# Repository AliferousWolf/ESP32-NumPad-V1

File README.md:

Included are all the files for the PCB and parts of the numpad v1 (Arduino IDE and KiCad)
------------------------
This is technically a prototype. The code is from various libraries and not very optomized, but it is a place to start.
To flash the ESP32 with the code, I used ArduinoIDE with the ESP32 boards added. When flashing, don't forget to download the libraries used within the code.

Parts used (part number):
------------------------
ESP 32 (NodeMCU-32S)
2x Encoder (PEC11L-4115F-S0020)
22x SMD diode (1N4148WS)
TFT display (Adafruit 4383)
mini sd card for tft display (technically optional)
24x mx switches depending on configuration
2x stabilizors depending on configuration

Optional for batery/bluetooth (part number)
------------------------
Switch (EG2208)
2x Capacitor 1uF (VJ1206Y105JXQTW1BC)
3.3v regulator (TC1264-3.3VDB)
10k resistor
6.8k resistor
3.3k resistor
battery

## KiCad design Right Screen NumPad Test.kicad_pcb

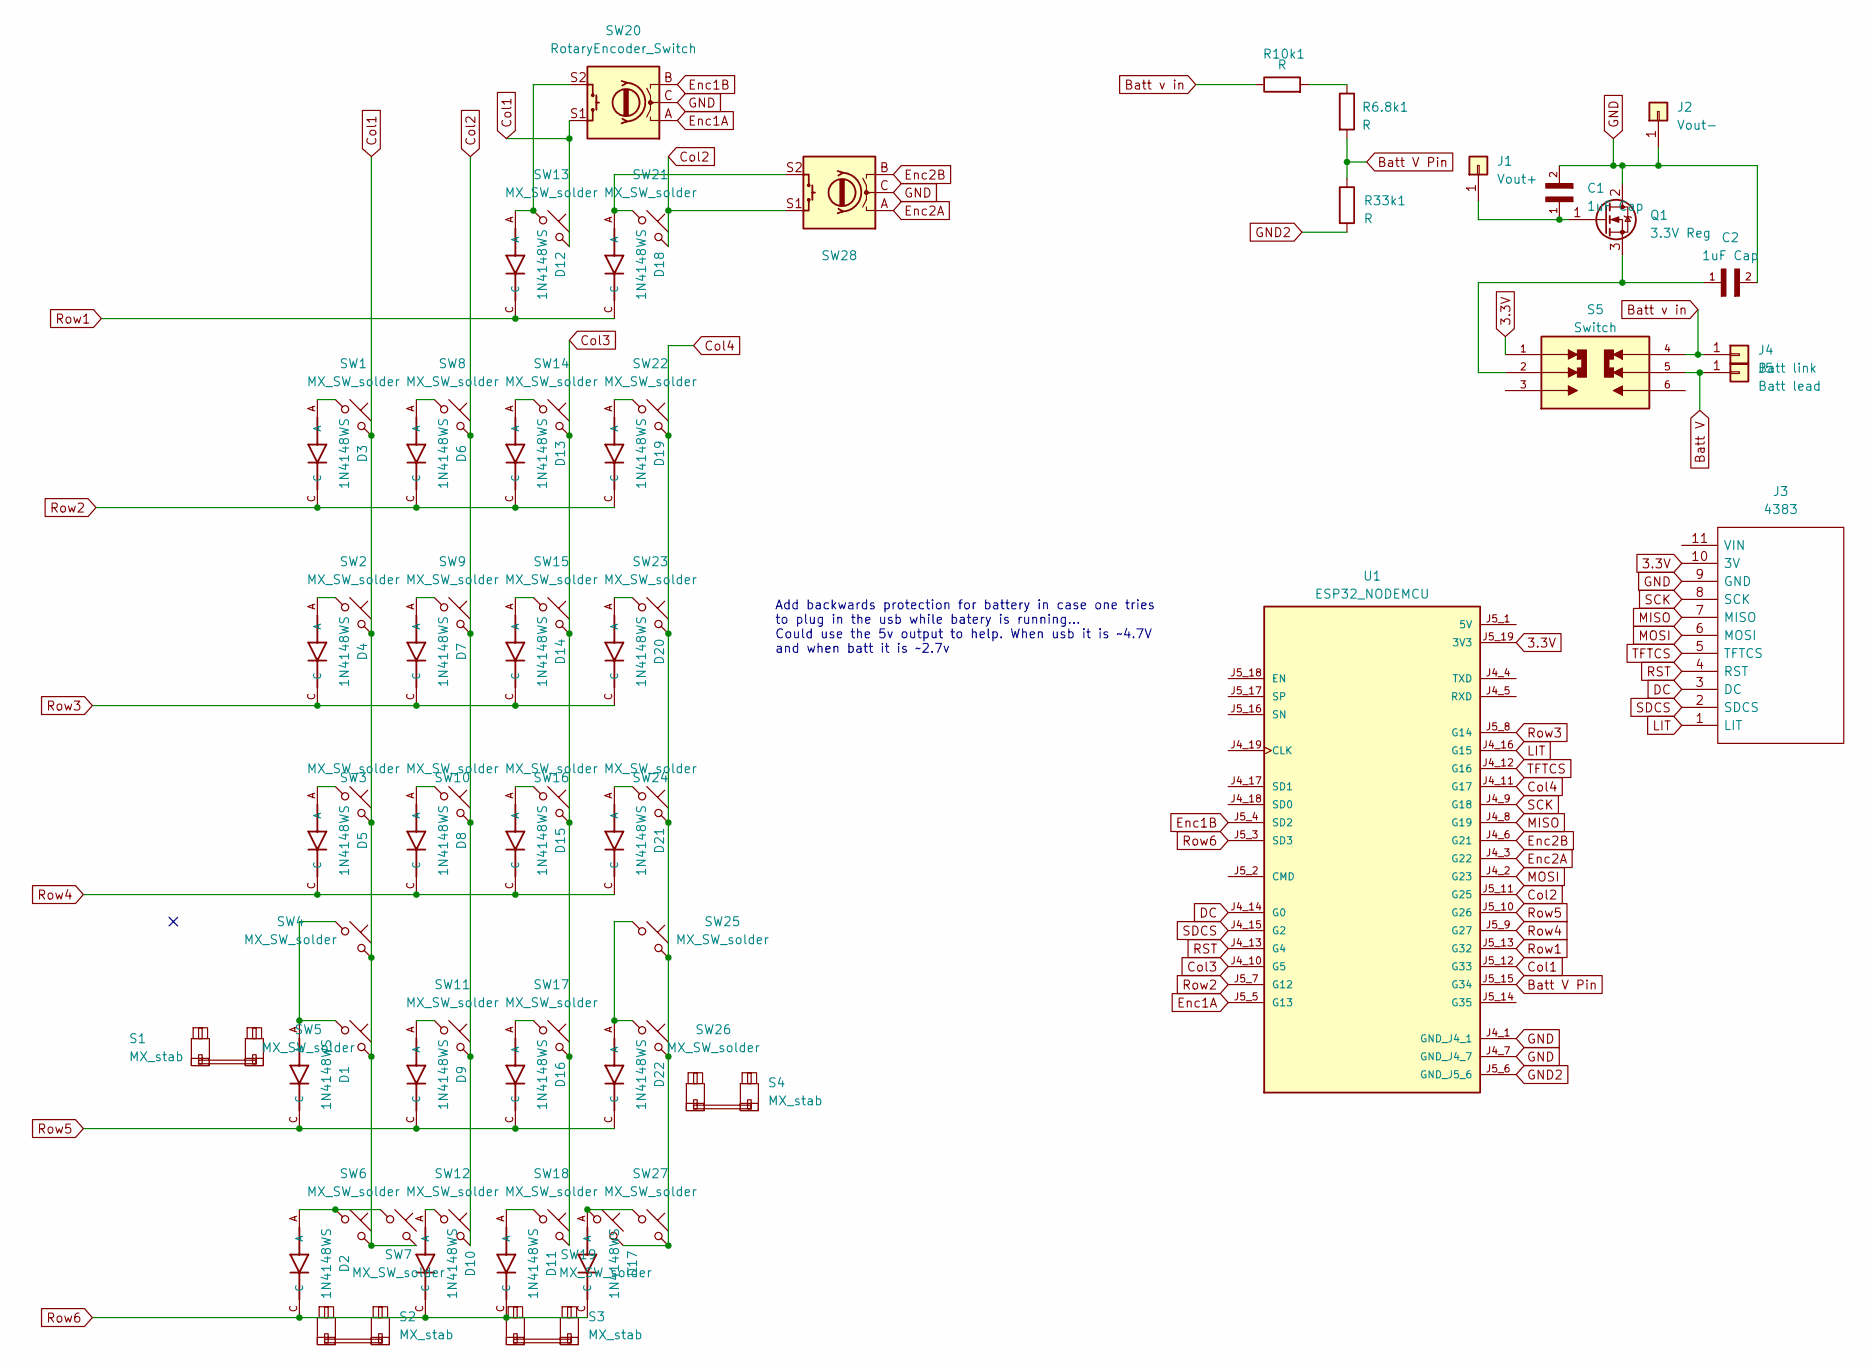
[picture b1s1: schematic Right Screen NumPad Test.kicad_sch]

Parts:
C1, C2: 1uF Cap; CAPC3216X170N
D1, D2, D3, D4, D5, D6, D7, D8, D9, D10, D11, D12, D13, D14, D15, D16, D17, D18, D19, D20, D21, D22: 1N4148WS; SODFL2512X100N
J1: Vout+; PinHeader_1x01_P2.00mm_Vertical
J2: Vout-; PinHeader_1x01_P2.00mm_Vertical
J3: 4383; Mouser Part Number 485-4383
J4: Batt link; PinHeader_1x01_P2.00mm_Vertical
J5: Batt lead; PinHeader_1x01_P2.00mm_Vertical
Q1: 3.3V Reg; SOT230P700X180-4N
R6.8k1, R10k1, R33k1: R; R_Axial_DIN0207_L6.3mm_D2.5mm_P10.16mm_Horizontal
S1, S2, S3, S4: MX_stab; STAB_MX_2u
S5: Switch; SW_EG2208; PARTREV C
SW1, SW2, SW3, SW4, SW5, SW6, SW7, SW8, SW9, SW10, SW11, SW12, SW13, SW14, SW15, SW16, SW17, SW18, SW19, SW21, SW22, SW23, SW24, SW25, SW26, SW27: MX_SW_solder; SW_MX_1u
SW20, SW28: RotaryEncoder_Switch; RotaryEncoder_Alps_EC11E-Switch_Vertical_H20mm
U1: ESP32_NODEMCU; MODULE_ESP32_NODEMCU

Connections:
3.3V: J3.10 (3V), S5.1, U1.J5_19 (3V3)
Batt V: J5.1, S5.5
Batt V Pin: R6.8k1.2, R33k1.1, U1.J5_15 (G34)
Batt v in: J4.1, R10k1.1, S5.4
Col1: SW1.2, SW2.2, SW3.2, SW4.2, SW5.2, SW6.2, SW7.2, SW13.2, SW20.S1, U1.J5_12 (G33)
Col2: SW8.2, SW9.2, SW10.2, SW11.2, SW12.2, SW21.2, SW28.S1, U1.J5_11 (G25)
Col3: SW14.2, SW15.2, SW16.2, SW17.2, SW18.2, U1.J4_10 (G5)
Col4: SW19.2, SW22.2, SW23.2, SW24.2, SW25.2, SW26.2, SW27.2, U1.J4_11 (G17)
DC: J3.3 (DC), U1.J4_14 (G0)
Enc1A: SW20.A, U1.J5_5 (G13)
Enc1B: SW20.B, U1.J5_4 (SD2)
Enc2A: SW28.A, U1.J4_3 (G22)
Enc2B: SW28.B, U1.J4_6 (G21)
GND: C1.2, C2.2, J2.1, J3.9 (GND), Q1.2 (D), SW20.C, SW28.C, U1.J4_1 (GND_J4_1), U1.J4_7 (GND_J4_7)
GND2: R33k1.2, U1.J5_6 (GND_J5_6)
LIT: J3.1 (LIT), U1.J4_16 (G15)
MISO: J3.7 (MISO), U1.J4_8 (G19)
MOSI: J3.6 (MOSI), U1.J4_2 (G23)
unnamed: D1.A, SW4.1, SW5.1
unnamed: D2.A, SW6.1, SW7.1
unnamed: D3.A, SW1.1
unnamed: D4.A, SW2.1
unnamed: D5.A, SW3.1
unnamed: D6.A, SW8.1
unnamed: D7.A, SW9.1
unnamed: D8.A, SW10.1
unnamed: D9.A, SW11.1
unnamed: D10.A, SW12.1
unnamed: D11.A, SW18.1
unnamed: D12.A, SW13.1, SW20.S2
unnamed: D13.A, SW14.1
unnamed: D14.A, SW15.1
unnamed: D15.A, SW16.1
unnamed: D16.A, SW17.1
unnamed: D17.A, SW19.1, SW27.1
unnamed: D18.A, SW21.1, SW28.S2
unnamed: D19.A, SW22.1
unnamed: D20.A, SW23.1
unnamed: D21.A, SW24.1
unnamed: D22.A, SW25.1, SW26.1
unnamed: C1.1, J1.1, Q1.1 (G)
unnamed: C2.1, Q1.3 (S), S5.2
unnamed: R6.8k1.1, R10k1.2
RST: J3.4 (RST), U1.J4_13 (G4)
Row1: D12.C, D18.C, U1.J5_13 (G32)
Row2: D3.C, D6.C, D13.C, D19.C, U1.J5_7 (G12)
Row3: D4.C, D7.C, D14.C, D20.C, U1.J5_8 (G14)
Row4: D5.C, D8.C, D15.C, D21.C, U1.J5_9 (G27)
Row5: D1.C, D9.C, D16.C, D22.C, U1.J5_10 (G26)
Row6: D2.C, D10.C, D11.C, D17.C, U1.J5_3 (SD3)
SCK: J3.8 (SCK), U1.J4_9 (G18)
SDCS: J3.2 (SDCS), U1.J4_15 (G2)
TFTCS: J3.5 (TFTCS), U1.J4_12 (G16)

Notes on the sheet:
Add backwards protection for battery in case one tries to plug in the usb while batery is running... Could use the 5v output to help. When usb it is ~4.7V and when batt it is ~2.7v

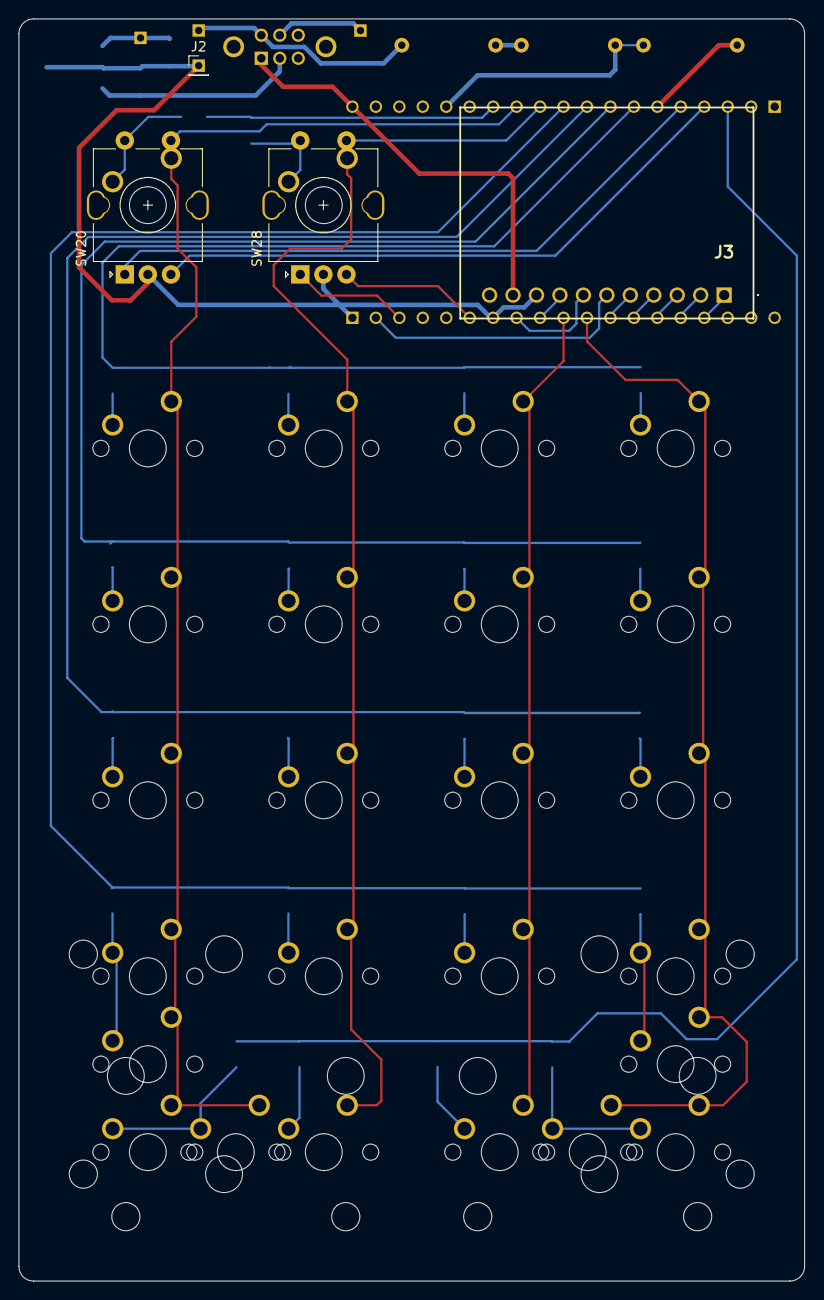
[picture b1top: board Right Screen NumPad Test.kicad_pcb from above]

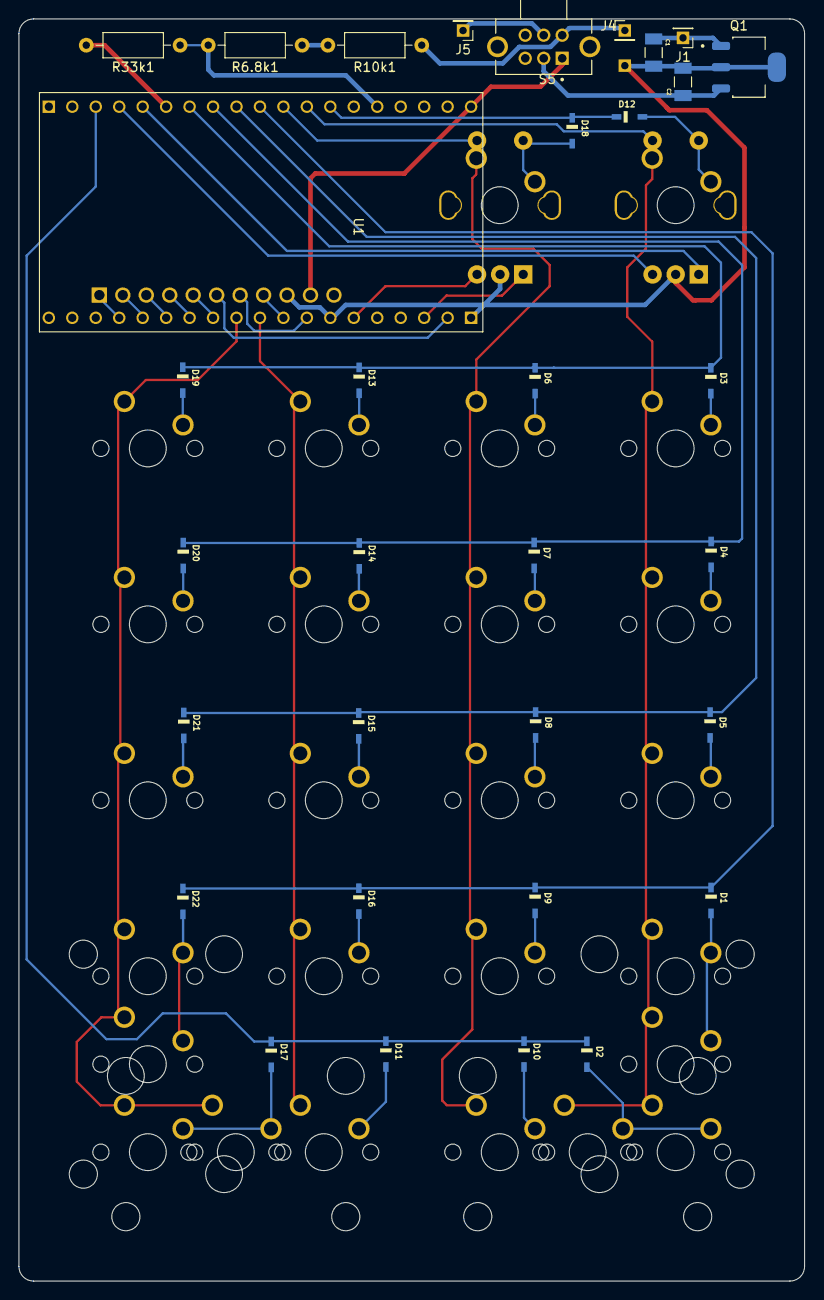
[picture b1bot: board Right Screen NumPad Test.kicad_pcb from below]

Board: 2 copper layers, 85.1 x 136.7 mm, 67 parts (33 on the bottom side), 53 nets.

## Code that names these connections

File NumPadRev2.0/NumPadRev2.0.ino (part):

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
//Keyboard

#define Row1 32 //pin RTCIO
#define Row2 12 //pin RTCIO
#define Row3 14 //pin RTCIO
#define Row4 27 //pin RTCIO
#define Row5 26 //pin RTCIO
#define Row6 10 //pin RTCIO

#define Col1 33 //pin
#define Col2 25 //pin 
#define Col3 5 //pin
#define Col4 17 //pin

const byte ROWS = 6;
const byte COLS = 4;
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};

byte rowPins[ROWS] = {Row1, Row2, Row3, Row4, Row5, Row6}; //diode direction is rows --> columns : annode on row side, cathode on column side
byte colPins[COLS] = {Col1, Col2, Col3, Col4};


Keypad kpd = Keypad( makeKeymap(keys), rowPins, colPins, ROWS, COLS ); //initiate keypad
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
  analogWrite(TFT_LIT, brightness); //start tft at brigthness level

  if(!SD.begin(2)){ //SDCS pin
    Serial.println("SD Card mount failed!"); //more messages to uncomment if needed.
    return;
  }
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
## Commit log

2023-12-28 Original file upload
    Files for numpad v1
2023-12-28 Adding arduino code
